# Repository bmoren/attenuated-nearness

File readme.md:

# Attenuated nearness
##### (aka. *52800*)
## Nearness with attenuators for each input

The idea is to have some number of input jacks (seven, here) mixed down to two output jacks, with each input representing a fixed pan position somewhere between the two extremes represented by the outputs. Plug a signal into the topmost input to send it entirely to the top output, the middle one to send it equally to both, etc.

Attenuated nearness builds on this original idea by adding a per input attenuator. This should give more flexibility in using this as a final or only mixing stage in small systems.

More info in this discussion on llllllll.co:
https://llllllll.co/t/prototyping-nearness-a-minimal-panning-mixer-module/8330

Original Nearness Repo: https://github.com/sarnesjo/nearness

## Build guide
1. Start with the surface-mount components. Mind the orientation of the ICs and diodes. (I like to do the whole backpack board first then the jack/pot board)
1. Solder the pin headers to join the 2 boards. (Be mindful of the socket/pin relationship if you are upgrading from a stock nearness.)
1. Place the jacks & pots on the PCB.
1. Screw on the panel, then solder jacks and pots.

## BOM
<a href="nearness_att_bom.csv">Build of Materials</a>

Mouser Project Link:	https://www.mouser.com/ProjectManager/ProjectDetail.aspx?AccessID=e1ea3fb0a7

## License
[CC BY-SA 4.0](http://creativecommons.org/licenses/by-sa/4.0/).    
Build and use at your own risk! I am not responsible for any damage to self or otherwise that arises from using this project!

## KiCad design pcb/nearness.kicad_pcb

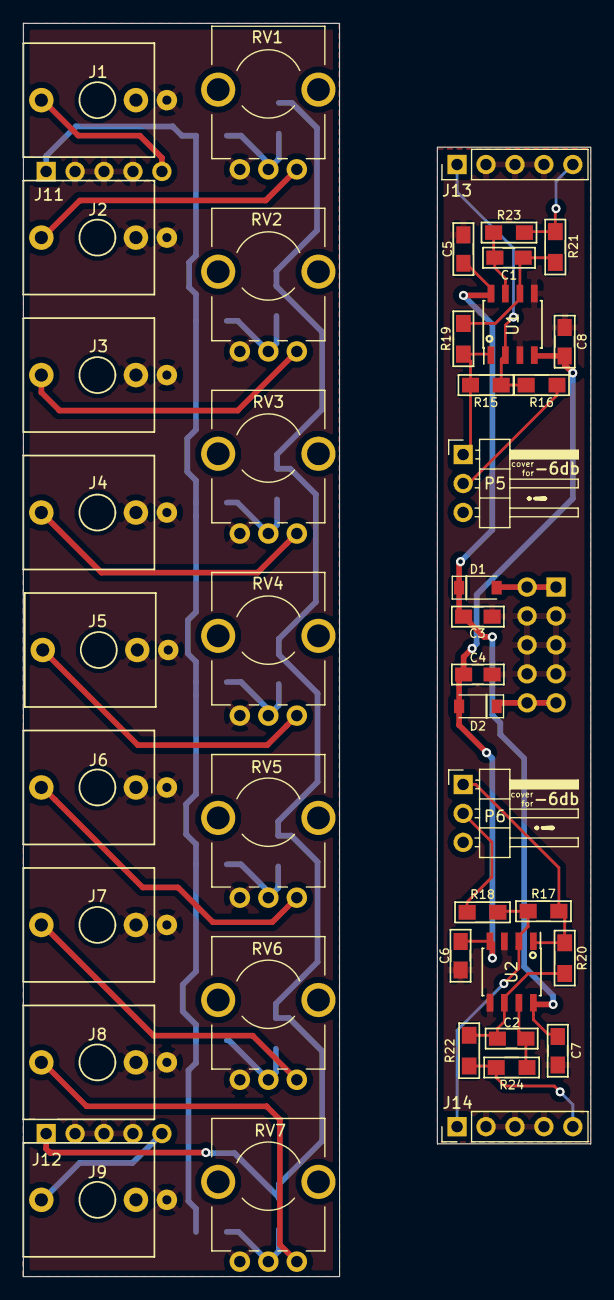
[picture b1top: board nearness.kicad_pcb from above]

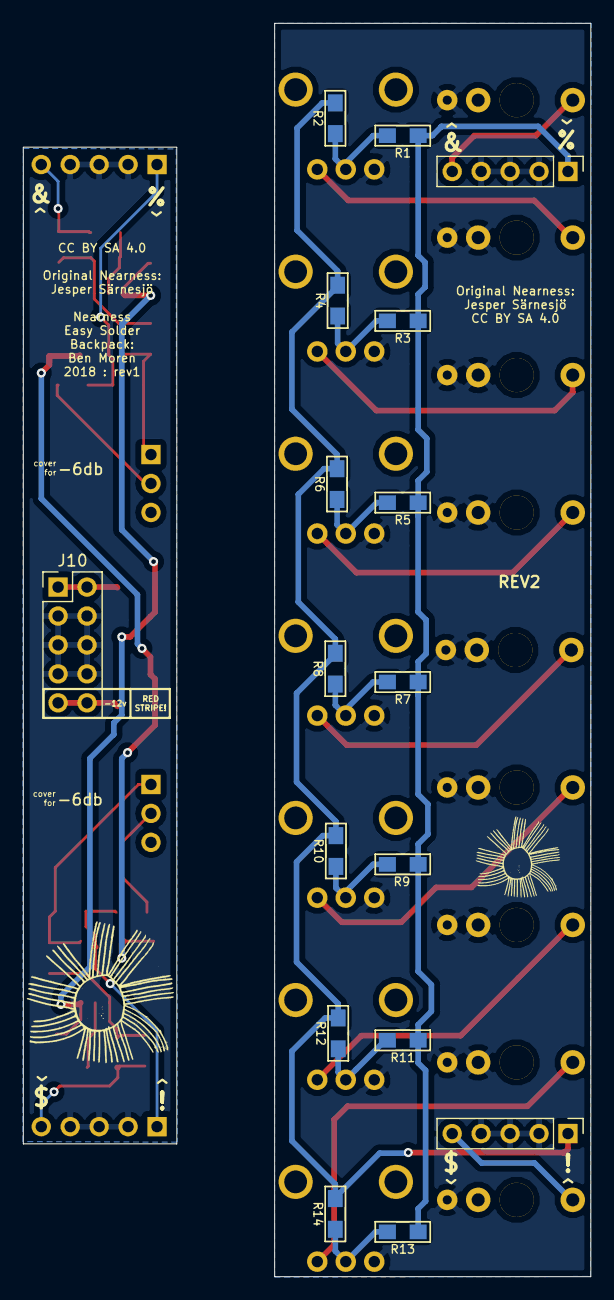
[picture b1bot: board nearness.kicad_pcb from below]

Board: 2 copper layers, 49.8 x 110.0 mm, 59 parts (17 on the bottom side), 35 nets.

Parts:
C1, C2: 22p; C_0805_HandSoldering_TopLabel
C3, C4: 22u; C_0805_HandSoldering_TopLabel
C5, C6, C7, C8: 100n; C_0805_HandSoldering_TopLabel
D1, D2: 1N5819HW; D_SOD-123
J1, J2, J3, J4, J5, J6, J7, J8, J9: PJ301M12; Thonkiconn_small_holes
J10: Conn_02x05_Odd_Even; Pin_Header_Straight_2x05_Pitch2.54mm
J11, J12: Conn_01x05; Pin_Header_Straight_1x05_Pitch2.54mm
J13, J14: Conn_01x05; Socket_Strip_Straight_1x05_Pitch2.54mm
P5, P6: CONN_01X03; Pin_Header_Angled_1x03_Pitch2.54mm
R1, R14, R15, R16, R17, R18, R19, R20, R21, R22: 100k; R_0805_HandSoldering_TopLabel
R2, R13: 1M67; R_0805_HandSoldering_TopLabel
R3, R12: 103k; R_0805_HandSoldering_TopLabel
R4, R11: 439k; R_0805_HandSoldering_TopLabel
R5, R10: 113k; R_0805_HandSoldering_TopLabel
R6, R9: 215k; R_0805_HandSoldering_TopLabel
R7, R8: 141k; R_0805_HandSoldering_TopLabel
R23, R24: 1k; R_0805_HandSoldering_TopLabel
RV1, RV2, RV3, RV4, RV5, RV6, RV7: POT; tall_trimmer_pot_9mm
U1, U2: LME49720; SOIC-8_3.9x4.9mm_Pitch1.27mm

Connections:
+12V: C3.1, C5.1, C7.1, D1.1, U1.8, U2.8
-12V: C4.2, C6.2, C8.2, D2.2, U1.4, U2.4
GND: C3.2, C4.1, C5.2, C6.1, C7.2, C8.1, J1.1, J2.1, J2.2, J3.1, J3.2, J4.1, J4.2, J5.1, J5.2, J6.1, J6.2, J7.1, J7.2, J8.1, J8.2, J9.1, J10.3, J10.4, J10.5, J10.6, J10.7, J10.8, J11.2, J11.3, J11.4, J12.2, J12.3, J12.4, J13.2, J13.3, J13.4, J14.2, J14.3, J14.4, RV1.1, RV2.1, RV3.1, RV4.1, RV5.1, RV6.1, RV7.1, U1.3, U1.5, U2.3, U2.5
unnamed: C1.1, R19.2, R21.1, U1.6
unnamed: C1.2, R23.1, U1.7
unnamed: C2.1, R20.2, R22.1, U2.6
unnamed: C2.2, R24.1, U2.7
unnamed: D1.2, J10.1, J10.2
unnamed: D2.1, J10.9, J10.10
unnamed: J1.3, J11.5
unnamed: J2.3, RV1.3
unnamed: J3.3, RV2.3
unnamed: J4.3, RV3.3
unnamed: J5.3, RV4.3
unnamed: J6.3, RV5.3
unnamed: J7.3, RV6.3
unnamed: J8.3, RV7.3
unnamed: J11.1, R1.2, R3.2, R5.2, R7.2, R9.2, R11.2, R13.2
unnamed: J12.1, R2.2, R4.2, R6.2, R8.2, R10.2, R12.2, R14.2
unnamed: J9.3, J12.5
unnamed: J13.1, R15.1, R16.1, U1.2
unnamed: J13.5, R21.2, R23.2
unnamed: J14.1, R17.1, R18.1, U2.2
unnamed: J14.5, R22.2, R24.2
unnamed: P5.1, R15.2, R19.1, U1.1
unnamed: P5.2, R16.2
unnamed: P6.1, R17.2, R20.1, U2.1
unnamed: P6.2, R18.2
unnamed: R1.1, R2.1, RV1.2
unnamed: R3.1, R4.1, RV2.2
unnamed: R5.1, R6.1, RV3.2
unnamed: R7.1, R8.1, RV4.2
unnamed: R9.1, R10.1, RV5.2
unnamed: R11.1, R12.1, RV6.2
unnamed: R13.1, R14.1, RV7.2

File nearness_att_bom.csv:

,Qnty,Value,Footprint,Description,Mouser Part #,Notes
"C1, C2, ",2,22p,0805,"Capacitor, ceramic, C0G/NP0, 50V, 1%",77-VJ0805A220FXACBC,
"C3, C4, ",2,22u,0805,"Capacitor, ceramic",81-GRM21BR61E226ME4L,Alternate: C2012JB1E226M125AC
"C5, C6, C7, C8, ",4,100n,0805,"Capacitor, ceramic",581-08053C104J,
"D1, D2, ",2,1N5819HW,SOD 123,Diode,621-1N5819HW-F,
"J2, J3, J4, J5, J6, J7, J8, J1, J9, ",9,PJ301M12,Thonkiconn,"""Thonkiconn"" switching mono phone jack",,https://modularaddict.com/parts/synth-diy-parts/pj301m12-jacks
"J10, ",1,Conn_02x05_Odd_Even,Header 2x05 Pitch 2.54mm,02x05,855-M20-9990546,2X 01x05
"J11, J12, ",2,Conn_01x05,Header 1x05 Pitch2.54mm,01x05,855-M20-9990546,
"J13, J14, ",2,Conn_01x05,Socket 1x05 Pitch2.54mm,01x05,855-M20-7820542,
"P5, P6, ",2,CONN_01X03,Header Angled 1x03 Pitch2.54mm,01x03,538-22-28-8034,
"R1, R14, R15, R16, R17, R18, R19, R20, R21, R22, ",10,100k,0805,"Resistor, thin film, 0.1%",667-ERA-6AEB104V,
"R2, R13, ",2,1M67,0805,"Resistor, thick film, 1%",667-ERJ-6ENF1694V,Original Nearness: 1M69K
"R3, R12, ",2,103k,0805,"Resistor, thin film, 0.1%",667-ERA-6AEB1023V,Original Nearness: 102K
"R4, R11, ",2,439k,0805,"Resistor, thin film, 0.1%",667-ERA-6AEB4423V,Original Nearness: 442k
"R5, R10, ",2,113k,0805,"Resistor, thin film, 0.1%",667-ERA-6AEB1133V,
"R6, R9, ",2,215k,0805,"Resistor, thin film, 0.1%",667-ERA-6AEB2153V,
"R7, R8, ",2,141k,0805,"Resistor, thin film, 0.1%",667-ERA-6AEB1403V,Original Nearness: 140K
"R23, R24, ",2,1k,0805,"Resistor, thin film, 0.1%",667-ERA-6AEB102V,
"RV1, RV2, RV3, RV4, RV5, RV6, RV7, ",7,A10K,tall trimmer pot 9mm,Potentiometer A10K,,https://modularaddict.com/parts/synth-diy-parts/9mm-tall-tri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
"U1, U2, ",2,LME49720,SOIC-8 3.9x4.9mm Pitch1.27mm,,926-LME49720MAX/NOPB,
Jumper,2,Jumper,,,,
,,,,,,
Component Count:,61,,,,,
Mouser Project Link,https://www.mouser.com/ProjectManager/ProjectDetail.aspx?Acc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,,,,,

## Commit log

2018-08-02 init
2018-08-02 readme
2018-08-02 add bom
2018-08-02 fix bom
